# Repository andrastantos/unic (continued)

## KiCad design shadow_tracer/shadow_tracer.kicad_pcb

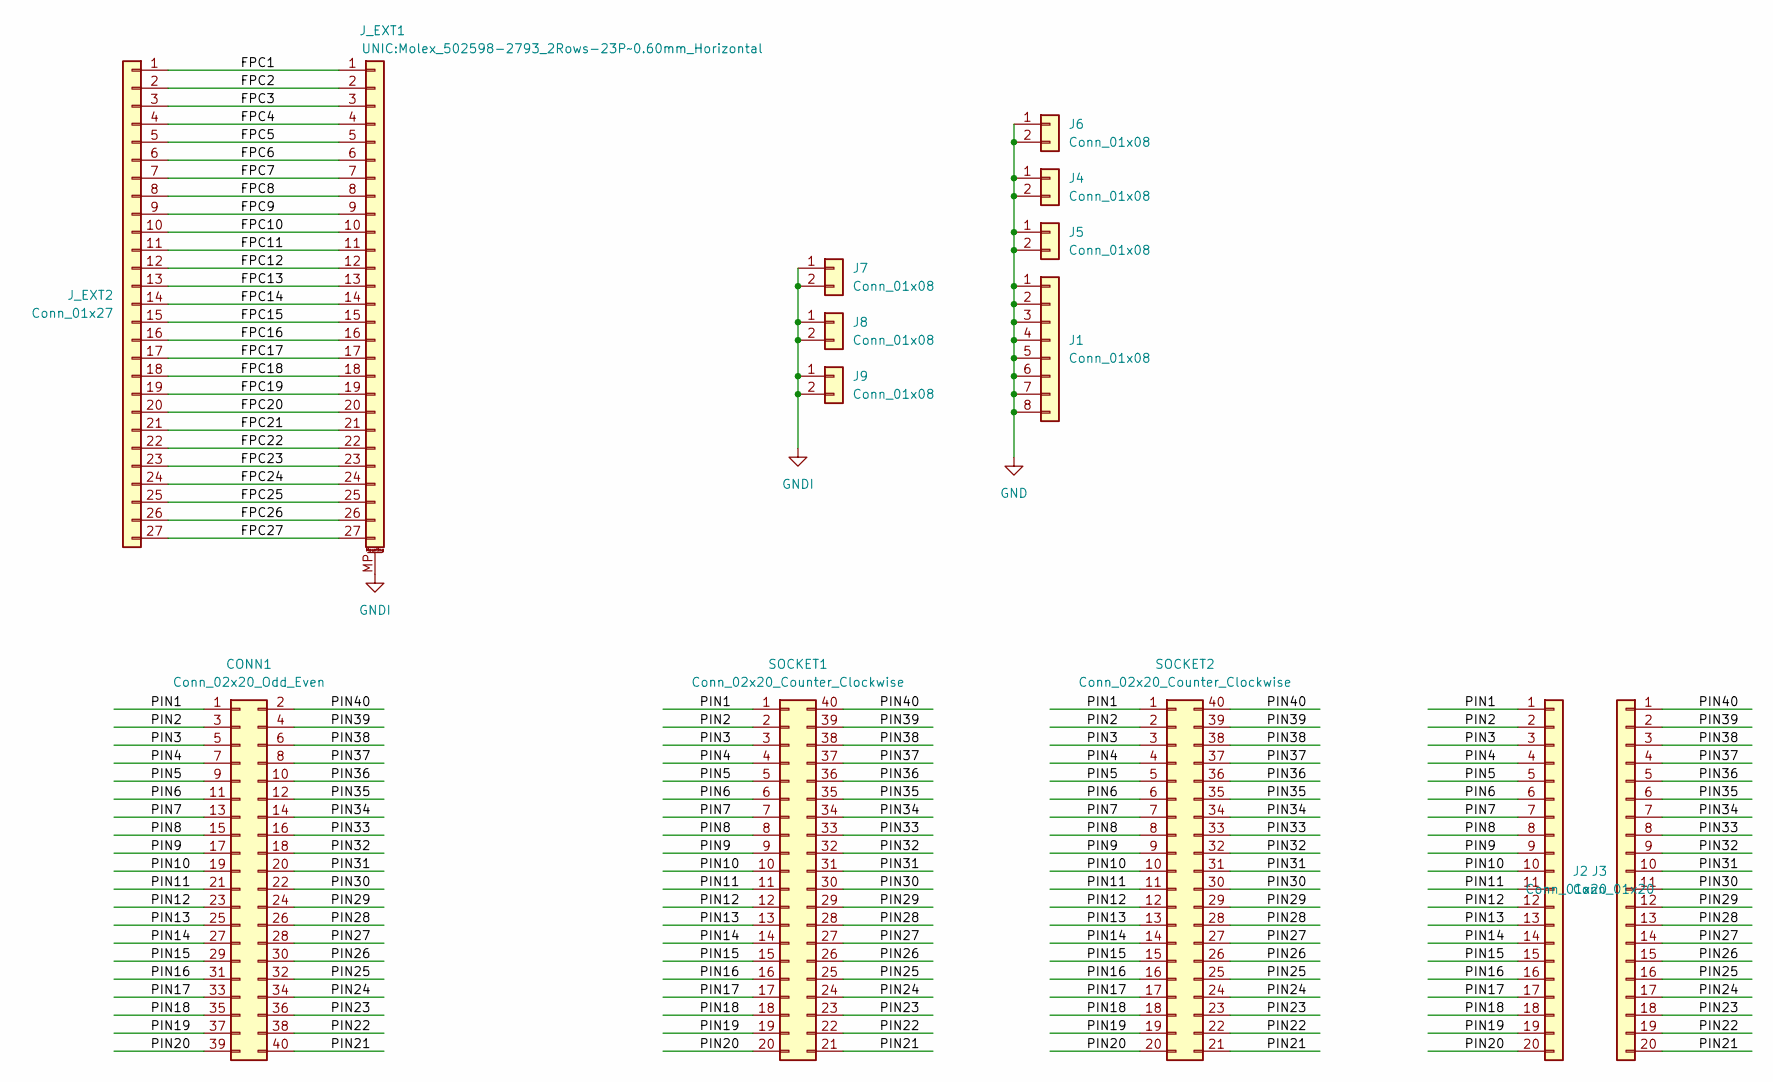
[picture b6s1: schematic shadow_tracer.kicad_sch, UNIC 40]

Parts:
CONN1: Conn_02x20_Odd_Even; PinSocket_2x20_P2.54mm_Horizontal
J1: Conn_01x08; PinHeader_1x08_P2.54mm_Vertical
J2, J3: Conn_01x20; PinHeader_1x20_P2.54mm_Vertical
J4, J5, J6, J7, J8, J9: Conn_01x08; PinHeader_1x02_P2.54mm_Vertical
J_EXT1: Conn_01x27_MountingPin; Molex_502598-2793_2Rows-23P~0.60mm_Horizontal
J_EXT2: Conn_01x27; PinHeader_2x14_P2.54mm_Vertical
SOCKET1, SOCKET2: Conn_02x20_Counter_Clockwise; DIP-40_W15.24mm_Socket_LongPads

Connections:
/FPC1: J_EXT1.1, J_EXT2.1
/FPC2: J_EXT1.2, J_EXT2.2
/FPC3: J_EXT1.3, J_EXT2.3
/FPC4: J_EXT1.4, J_EXT2.4
/FPC5: J_EXT1.5, J_EXT2.5
/FPC6: J_EXT1.6, J_EXT2.6
/FPC7: J_EXT1.7, J_EXT2.7
/FPC8: J_EXT1.8, J_EXT2.8
/FPC9: J_EXT1.9, J_EXT2.9
/FPC10: J_EXT1.10, J_EXT2.10
/FPC11: J_EXT1.11, J_EXT2.11
/FPC12: J_EXT1.12, J_EXT2.12
/FPC13: J_EXT1.13, J_EXT2.13
/FPC14: J_EXT1.14, J_EXT2.14
/FPC15: J_EXT1.15, J_EXT2.15
/FPC16: J_EXT1.16, J_EXT2.16
/FPC17: J_EXT1.17, J_EXT2.17
/FPC18: J_EXT1.18, J_EXT2.18
/FPC19: J_EXT1.19, J_EXT2.19
/FPC20: J_EXT1.20, J_EXT2.20
/FPC21: J_EXT1.21, J_EXT2.21
/FPC22: J_EXT1.22, J_EXT2.22
/FPC23: J_EXT1.23, J_EXT2.23
/FPC24: J_EXT1.24, J_EXT2.24
/FPC25: J_EXT1.25, J_EXT2.25
/FPC26: J_EXT1.26, J_EXT2.26
/FPC27: J_EXT1.27, J_EXT2.27
/PIN1: CONN1.1, J2.1, SOCKET1.1, SOCKET2.1
/PIN2: CONN1.3, J2.2, SOCKET1.2, SOCKET2.2
/PIN3: CONN1.5, J2.3, SOCKET1.3, SOCKET2.3
/PIN4: CONN1.7, J2.4, SOCKET1.4, SOCKET2.4
/PIN5: CONN1.9, J2.5, SOCKET1.5, SOCKET2.5
/PIN6: CONN1.11, J2.6, SOCKET1.6, SOCKET2.6
/PIN7: CONN1.13, J2.7, SOCKET1.7, SOCKET2.7
/PIN8: CONN1.15, J2.8, SOCKET1.8, SOCKET2.8
/PIN9: CONN1.17, J2.9, SOCKET1.9, SOCKET2.9
/PIN10: CONN1.19, J2.10, SOCKET1.10, SOCKET2.10
/PIN11: CONN1.21, J2.11, SOCKET1.11, SOCKET2.11
/PIN12: CONN1.23, J2.12, SOCKET1.12, SOCKET2.12
/PIN13: CONN1.25, J2.13, SOCKET1.13, SOCKET2.13
/PIN14: CONN1.27, J2.14, SOCKET1.14, SOCKET2.14
/PIN15: CONN1.29, J2.15, SOCKET1.15, SOCKET2.15
/PIN16: CONN1.31, J2.16, SOCKET1.16, SOCKET2.16
/PIN17: CONN1.33, J2.17, SOCKET1.17, SOCKET2.17
/PIN18: CONN1.35, J2.18, SOCKET1.18, SOCKET2.18
/PIN19: CONN1.37, J2.19, SOCKET1.19, SOCKET2.19
/PIN20: CONN1.39, J2.20, SOCKET1.20, SOCKET2.20
/PIN21: CONN1.40, J3.20, SOCKET1.21, SOCKET2.21
/PIN22: CONN1.38, J3.19, SOCKET1.22, SOCKET2.22
/PIN23: CONN1.36, J3.18, SOCKET1.23, SOCKET2.23
/PIN24: CONN1.34, J3.17, SOCKET1.24, SOCKET2.24
/PIN25: CONN1.32, J3.16, SOCKET1.25, SOCKET2.25
/PIN26: CONN1.30, J3.15, SOCKET1.26, SOCKET2.26
/PIN27: CONN1.28, J3.14, SOCKET1.27, SOCKET2.27
/PIN28: CONN1.26, J3.13, SOCKET1.28, SOCKET2.28
/PIN29: CONN1.24, J3.12, SOCKET1.29, SOCKET2.29
/PIN30: CONN1.22, J3.11, SOCKET1.30, SOCKET2.30
/PIN31: CONN1.20, J3.10, SOCKET1.31, SOCKET2.31
/PIN32: CONN1.18, J3.9, SOCKET1.32, SOCKET2.32
/PIN33: CONN1.16, J3.8, SOCKET1.33, SOCKET2.33
/PIN34: CONN1.14, J3.7, SOCKET1.34, SOCKET2.34
/PIN35: CONN1.12, J3.6, SOCKET1.35, SOCKET2.35
/PIN36: CONN1.10, J3.5, SOCKET1.36, SOCKET2.36
/PIN37: CONN1.8, J3.4, SOCKET1.37, SOCKET2.37
/PIN38: CONN1.6, J3.3, SOCKET1.38, SOCKET2.38
/PIN39: CONN1.4, J3.2, SOCKET1.39, SOCKET2.39
/PIN40: CONN1.2, J3.1, SOCKET1.40, SOCKET2.40
GND: J1.1, J1.2, J1.3, J1.4, J1.5, J1.6, J1.7, J1.8, J4.1, J4.2, J5.1, J5.2, J6.1, J6.2
GNDI: J7.1, J7.2, J8.1, J8.2, J9.1, J9.2, J_EXT1.MP (MountPin)

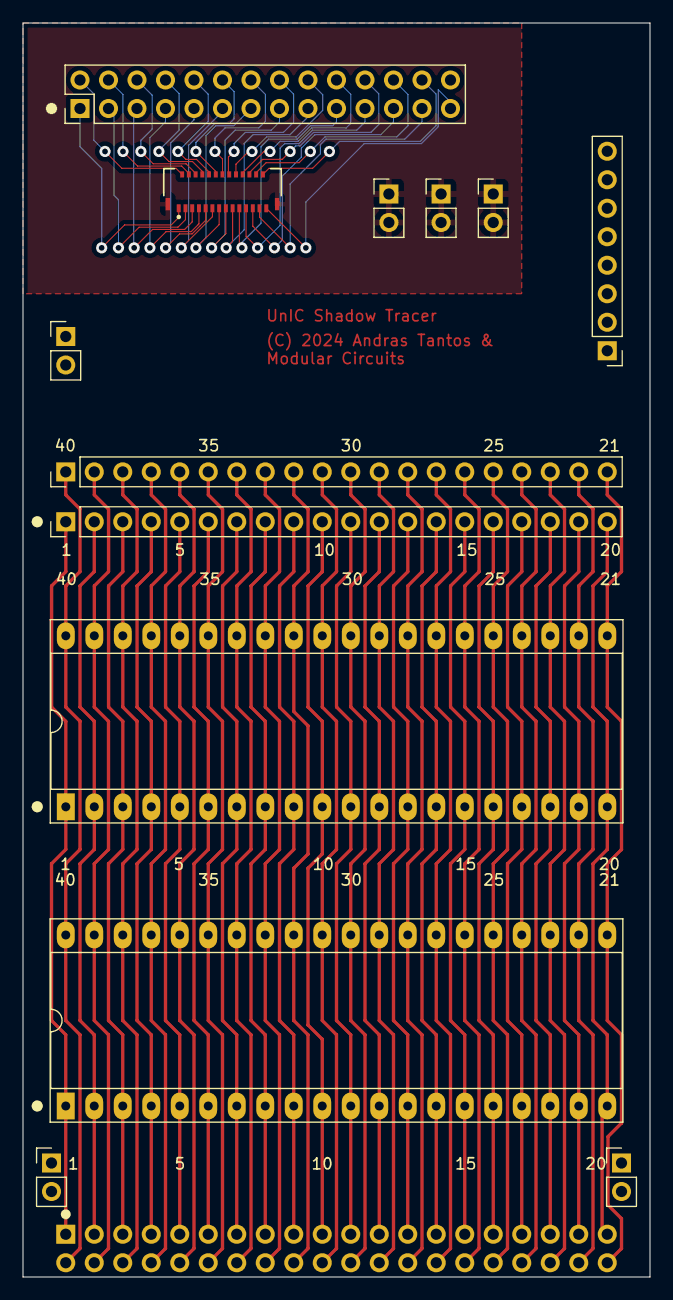
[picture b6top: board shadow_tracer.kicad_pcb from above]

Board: 2 copper layers, 55.9 x 111.8 mm, 14 parts (0 on the bottom side), 69 nets.

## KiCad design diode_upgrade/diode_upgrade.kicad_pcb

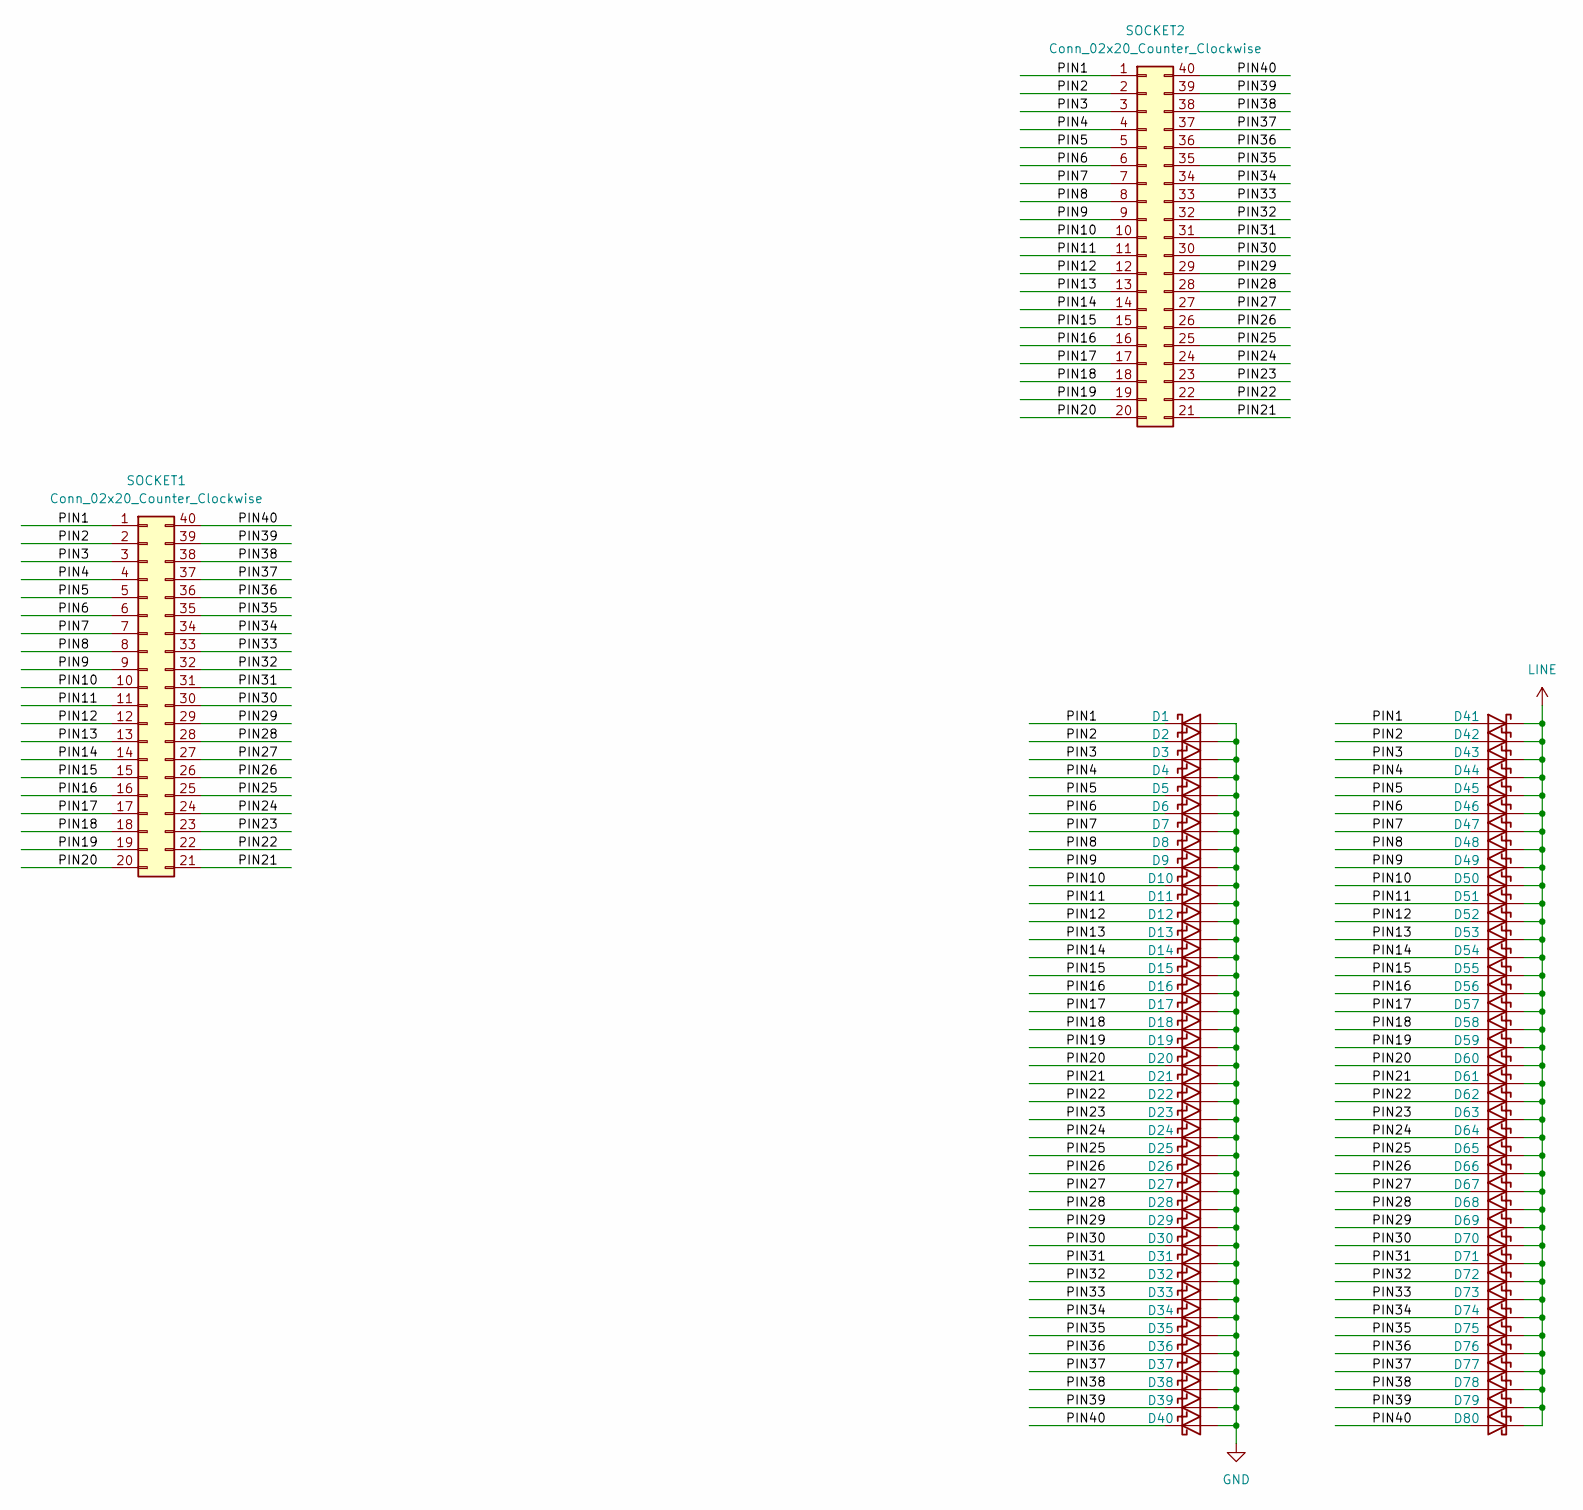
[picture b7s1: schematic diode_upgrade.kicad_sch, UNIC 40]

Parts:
D1, D2, D3, D4, D5, D6, D7, D8, D9, D10, D11, D12, D13, D14, D15, D16, D17, D18, D19, D20, D21, D22, D23, D24, D25, D26, D27, D28, D29, D30, D31, D32, D33, D34, D35, D36, D37, D38, D39, D40, D41, D42, D43, D44, D45, D46, D47, D48, D49, D50, D51, D52, D53, D54, D55, D56, D57, D58, D59, D60, D61, D62, D63, D64, D65, D66, D67, D68, D69, D70, D71, D72, D73, D74, D75, D76, D77, D78, D79, D80: D_Schottky; D_SOD-123; mpn SM5817PL-TP
SOCKET1: Conn_02x20_Counter_Clockwise; DIP-40_pin_header; mpn BA3760-TUBL-4A-F5
SOCKET2: Conn_02x20_Counter_Clockwise; DIP-40_W15.24mm_Socket_LongPads

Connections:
/PIN1: D1.1 (K), D41.2 (A), SOCKET1.1, SOCKET2.1
/PIN2: D2.1 (K), D42.2 (A), SOCKET1.2, SOCKET2.2
/PIN3: D3.1 (K), D43.2 (A), SOCKET1.3, SOCKET2.3
/PIN4: D4.1 (K), D44.2 (A), SOCKET1.4, SOCKET2.4
/PIN5: D5.1 (K), D45.2 (A), SOCKET1.5, SOCKET2.5
/PIN6: D6.1 (K), D46.2 (A), SOCKET1.6, SOCKET2.6
/PIN7: D7.1 (K), D47.2 (A), SOCKET1.7, SOCKET2.7
/PIN8: D8.1 (K), D48.2 (A), SOCKET1.8, SOCKET2.8
/PIN9: D9.1 (K), D49.2 (A), SOCKET1.9, SOCKET2.9
/PIN10: D10.1 (K), D50.2 (A), SOCKET1.10, SOCKET2.10
/PIN11: D11.1 (K), D51.2 (A), SOCKET1.11, SOCKET2.11
/PIN12: D12.1 (K), D52.2 (A), SOCKET1.12, SOCKET2.12
/PIN13: D13.1 (K), D53.2 (A), SOCKET1.13, SOCKET2.13
/PIN14: D14.1 (K), D54.2 (A), SOCKET1.14, SOCKET2.14
/PIN15: D15.1 (K), D55.2 (A), SOCKET1.15, SOCKET2.15
/PIN16: D16.1 (K), D56.2 (A), SOCKET1.16, SOCKET2.16
/PIN17: D17.1 (K), D57.2 (A), SOCKET1.17, SOCKET2.17
/PIN18: D18.1 (K), D58.2 (A), SOCKET1.18, SOCKET2.18
/PIN19: D19.1 (K), D59.2 (A), SOCKET1.19, SOCKET2.19
/PIN20: D20.1 (K), D60.2 (A), SOCKET1.20, SOCKET2.20
/PIN21: D21.1 (K), D61.2 (A), SOCKET1.21, SOCKET2.21
/PIN22: D22.1 (K), D62.2 (A), SOCKET1.22, SOCKET2.22
/PIN23: D23.1 (K), D63.2 (A), SOCKET1.23, SOCKET2.23
/PIN24: D24.1 (K), D64.2 (A), SOCKET1.24, SOCKET2.24
/PIN25: D25.1 (K), D65.2 (A), SOCKET1.25, SOCKET2.25
/PIN26: D26.1 (K), D66.2 (A), SOCKET1.26, SOCKET2.26
/PIN27: D27.1 (K), D67.2 (A), SOCKET1.27, SOCKET2.27
/PIN28: D28.1 (K), D68.2 (A), SOCKET1.28, SOCKET2.28
/PIN29: D29.1 (K), D69.2 (A), SOCKET1.29, SOCKET2.29
/PIN30: D30.1 (K), D70.2 (A), SOCKET1.30, SOCKET2.30
/PIN31: D31.1 (K), D71.2 (A), SOCKET1.31, SOCKET2.31
/PIN32: D32.1 (K), D72.2 (A), SOCKET1.32, SOCKET2.32
/PIN33: D33.1 (K), D73.2 (A), SOCKET1.33, SOCKET2.33
/PIN34: D34.1 (K), D74.2 (A), SOCKET1.34, SOCKET2.34
/PIN35: D35.1 (K), D75.2 (A), SOCKET1.35, SOCKET2.35
/PIN36: D36.1 (K), D76.2 (A), SOCKET1.36, SOCKET2.36
/PIN37: D37.1 (K), D77.2 (A), SOCKET1.37, SOCKET2.37
/PIN38: D38.1 (K), D78.2 (A), SOCKET1.38, SOCKET2.38
/PIN39: D39.1 (K), D79.2 (A), SOCKET1.39, SOCKET2.39
/PIN40: D40.1 (K), D80.2 (A), SOCKET1.40, SOCKET2.40
GND: D1.2 (A), D2.2 (A), D3.2 (A), D4.2 (A), D5.2 (A), D6.2 (A), D7.2 (A), D8.2 (A), D9.2 (A), D10.2 (A), D11.2 (A), D12.2 (A), D13.2 (A), D14.2 (A), D15.2 (A), D16.2 (A), D17.2 (A), D18.2 (A), D19.2 (A), D20.2 (A), D21.2 (A), D22.2 (A), D23.2 (A), D24.2 (A), D25.2 (A), D26.2 (A), D27.2 (A), D28.2 (A), D29.2 (A), D30.2 (A), D31.2 (A), D32.2 (A), D33.2 (A), D34.2 (A), D35.2 (A), D36.2 (A), D37.2 (A), D38.2 (A), D39.2 (A), D40.2 (A)
LINE: D41.1 (K), D42.1 (K), D43.1 (K), D44.1 (K), D45.1 (K), D46.1 (K), D47.1 (K), D48.1 (K), D49.1 (K), D50.1 (K), D51.1 (K), D52.1 (K), D53.1 (K), D54.1 (K), D55.1 (K), D56.1 (K), D57.1 (K), D58.1 (K), D59.1 (K), D60.1 (K), D61.1 (K), D62.1 (K), D63.1 (K), D64.1 (K), D65.1 (K), D66.1 (K), D67.1 (K), D68.1 (K), D69.1 (K), D70.1 (K), D71.1 (K), D72.1 (K), D73.1 (K), D74.1 (K), D75.1 (K), D76.1 (K), D77.1 (K), D78.1 (K), D79.1 (K), D80.1 (K)

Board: 2 copper layers, 82 parts (40 on the bottom side), 42 nets, no tracks yet.

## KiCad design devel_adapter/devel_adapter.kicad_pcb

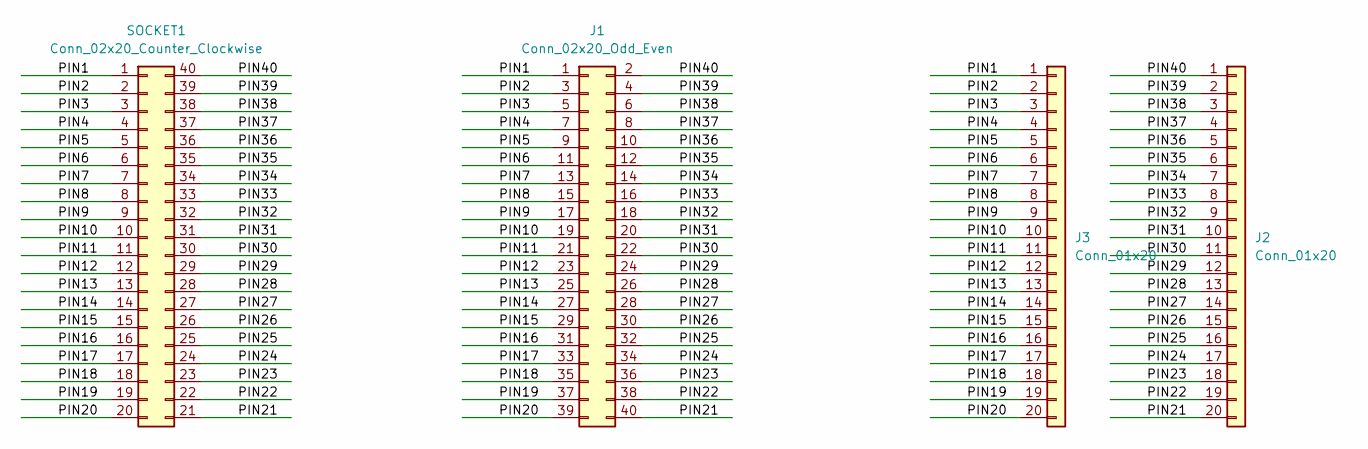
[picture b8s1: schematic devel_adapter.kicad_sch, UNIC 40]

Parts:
J1: Conn_02x20_Odd_Even; PinHeader_2x20_P2.54mm_Vertical
J2, J3: Conn_01x20; PinHeader_1x20_P2.54mm_Vertical
SOCKET1: Conn_02x20_Counter_Clockwise; DIP-40_pin_header

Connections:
/PIN1: J1.1, J3.1, SOCKET1.1
/PIN2: J1.3, J3.2, SOCKET1.2
/PIN3: J1.5, J3.3, SOCKET1.3
/PIN4: J1.7, J3.4, SOCKET1.4
/PIN5: J1.9, J3.5, SOCKET1.5
/PIN6: J1.11, J3.6, SOCKET1.6
/PIN7: J1.13, J3.7, SOCKET1.7
/PIN8: J1.15, J3.8, SOCKET1.8
/PIN9: J1.17, J3.9, SOCKET1.9
/PIN10: J1.19, J3.10, SOCKET1.10
/PIN11: J1.21, J3.11, SOCKET1.11
/PIN12: J1.23, J3.12, SOCKET1.12
/PIN13: J1.25, J3.13, SOCKET1.13
/PIN14: J1.27, J3.14, SOCKET1.14
/PIN15: J1.29, J3.15, SOCKET1.15
/PIN16: J1.31, J3.16, SOCKET1.16
/PIN17: J1.33, J3.17, SOCKET1.17
/PIN18: J1.35, J3.18, SOCKET1.18
/PIN19: J1.37, J3.19, SOCKET1.19
/PIN20: J1.39, J3.20, SOCKET1.20
/PIN21: J1.40, J2.20, SOCKET1.21
/PIN22: J1.38, J2.19, SOCKET1.22
/PIN23: J1.36, J2.18, SOCKET1.23
/PIN24: J1.34, J2.17, SOCKET1.24
/PIN25: J1.32, J2.16, SOCKET1.25
/PIN26: J1.30, J2.15, SOCKET1.26
/PIN27: J1.28, J2.14, SOCKET1.27
/PIN28: J1.26, J2.13, SOCKET1.28
/PIN29: J1.24, J2.12, SOCKET1.29
/PIN30: J1.22, J2.11, SOCKET1.30
/PIN31: J1.20, J2.10, SOCKET1.31
/PIN32: J1.18, J2.9, SOCKET1.32
/PIN33: J1.16, J2.8, SOCKET1.33
/PIN34: J1.14, J2.7, SOCKET1.34
/PIN35: J1.12, J2.6, SOCKET1.35
/PIN36: J1.10, J2.5, SOCKET1.36
/PIN37: J1.8, J2.4, SOCKET1.37
/PIN38: J1.6, J2.3, SOCKET1.38
/PIN39: J1.4, J2.2, SOCKET1.39
/PIN40: J1.2, J2.1, SOCKET1.40

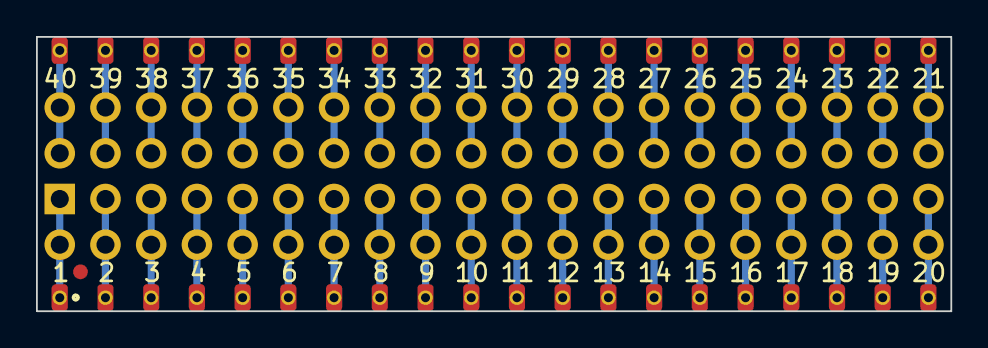
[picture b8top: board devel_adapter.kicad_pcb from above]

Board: 2 copper layers, 50.8 x 15.2 mm, 4 parts (0 on the bottom side), 40 nets.

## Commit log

2023-05-09 Unic project started.
2023-05-09 Whops, gitignore got to the wrong place.
2023-05-09 Gitignore updates.
2023-05-11 Added JTAG notes
2023-05-11 PCB file for unic
2023-05-11 Various datasheets added.
2023-05-12 More datasheets
2023-05-15 Added summary package datasheet.
2023-06-07 Added JFET-based protection sim. It seems to be working?
2023-06-16 Documentation update.
2023-06-26 More info on protection circuits.
2023-06-28 Large documentation update
2023-12-11 Much missing stuff added back
2023-12-11 Migrated cores
2023-12-11 Re-added submodules
2023-12-11 Added ESD diode from within FPGA.
    There is a transient on this diode when
    driven high hard from an external source.
    The length of the transient is about 7ns.
2023-12-13 Changed Espresso, added 8088 project.
2023-12-13 Added extra diodes to shunt ESD path.
2023-12-13 More simulation of high-voltage transients.
2023-12-19 GW1-based board is fully routed. Cleanup still needed!
2023-12-19 Some more sim experiments
2023-12-20 Much more GoWin documentation.
2023-12-20 Small fixes to board file
2023-12-20 Migrated to KiCad 7.
2023-12-20 Fixed GoWin part footprint reference.
2023-12-21 Board more or less done.
2023-12-25 Development board more or less done.
2023-12-25 Library changes related to development board.
2023-12-26 DIP adapter board for development board.
2023-12-26 Adapter board is production ready
2023-12-26 Added tiny DAC to library
2023-12-26 Devel board is production ready
2023-12-27 Added power input connector
2023-12-27 Added power jack with 3D model
2023-12-28 Replaced TSSOP FLASH with SO-8 one due to availability concerns.
2023-12-29 Updated FLASH part to package that's actually available.
2023-12-29 Updated footprints for LCD connector and PSRAM
2023-12-29 Populated part numbers for most parts.
2023-12-30 Reworked switcher components and layout.
2023-12-30 Switched back to 0805 caps: they're cheaper. TODO: part number updates.
2024-01-04 Ready to roll with DEVEL board!
2024-02-12 New documentation
2024-02-12 Devel updates.
2024-02-12 BOM checked in
2024-02-12 First FPGA project.
    This is also an attempt at a universal CST file, but the toolset is too
    brain-dead to allow for that. I will have to auto-generate this from
    a template once the Python flow is worked out.
2024-02-12 Code for first OLED test. Not tested in real HW, but simulation is promising.
2024-02-12 Some updated to UNIC GW1 based on post-release learnings.
2024-02-13 OLED controller works.
2024-02-15 Added PNG parser to OLED driver; added logo as well.
2024-02-16 Some outstanding changes to T13 board
2024-03-26 Simulation circuit updates.
2024-04-30 Updated board file; started cover CAD.
    This checkin marks the hopefully complete V1.0 design for the form-factor
    board.
    It also contains the first (incomplete) iteration of the cover design.
    It has a bunch of interference with components on the PCB which
    needs to be cleaned. It's also unclear if snaps have to be 1.5mm thick.
    Seems excessive. Finally, I don't think the OLED display can even survive
2024-05-01 Added test-points, edge clearance, some cleanup.
2024-05-03 Added fiducials and some other flourishes.
2024-05-05 Lots of (local) footprint cleanup and readying for board release.
2024-05-05 DRC-clean DIP-40 header.
2024-05-05 Fixed some footprints, fab drawings.
2024-05-31 Fixed GoWin part number
2024-05-31 Release files.
2024-05-31 Documentation drawings
2024-06-05 Changed PCB to match that of manufacturing:
    1. Removed solder paste from U1 (as it will be hand-soldered).
    2. Changed vias to have pads on top/bottom.
2024-08-04 ECO for switcher part change
2024-08-09 New diodes are added
    PCB is also fixed up, but fab notes
    need cleaning. Also, I need to select
    an actual diode.
2024-08-09 Updated diode part and footprint.
2024-08-09 Fixed fab notes
2024-08-12 Added some new datasheets.
2024-08-12 Started RP2350-based UnIC.
2024-08-12 Some diode simulations.
2024-08-12 Small DIP exercises.
2024-08-12 More work towards RP based UnIC
    The IO connections are mostly figured out, component placement
    as well. Still need new inductor, proper XTAL, USB and of course
    a lot of routing, including power.
2024-08-13 More work towards UnIC-RP. This time power supplies are cleaned up a bit.
2024-08-13 Some notes about SWDBG over USB-C
2024-08-13 Much more complet RP schematic.
    The USB-based debug setup is now drawn up. Component
    placement is also complete. A thorough review is needed
    especially on component footprints!
2024-08-14 More notes, this time with actual repro in LA.
2024-08-14 Missed USB connector model.
2024-08-14 Lots of work towards PIP issues.
2024-08-14 More work towards routing RP board.
2024-08-15 More or less complete schematic.
    Component selection is not final, but functionality around
    USB-C connector is. We even have UART output on it now as
    well as USB VBUS detection and control on the right pins.
2024-08-15 Component selection I think now is complete.
2024-08-15 Board fully routed except for power.
2024-08-16 Work towards power routing
2024-08-16 More or less complete routing.
    There are a few clearance violations with NPTH that doesn't
    make sense. Also, power planes are not in yet, only wires.
2024-08-18 Shadow tracer board.
    This is a board that (with the proper core) can shadow a to-be-simulated
    IC with its UnIC equivalent and trigger on any waveform mismatches.
    It can be used to quickly track down differences in behavior between
    the real and the UnIC versions of implementations.
2024-08-18 More notes on experiments.
2024-08-19 Diode upgrade PCB.
    This little guy would go underneath a UnIC V1.0 board
    and upgrade all the diodes with proper Schottky ones.
    Then GND and LINE wold need to be blue-wired over to
    UnIC to make the whole contraption work.
2024-08-20 Programmer more or less complete.
    Missing LEDs, I guess.
2024-08-20 Release package for programmer.
2024-08-20 True release package for programmer.
2024-08-21 Added BOM notes
2024-08-21 Shadow tracer release package.
2024-09-03 Much UnIC RP cleanup.
2024-09-04 Second programmer variant.
2024-09-04 Finished programmer 2.
2024-09-04 Beautified schematic and PCB for programmer 2.
2024-09-08 Some note updates
2024-09-08 Programmer bring-up changes and notes
2024-09-08 Updated programmer schematic and PCBs.
    All known changes are incorporated.
    p.s.: I decided to stick with this rather sketchy LDO.
    The reason for this is that it's heatsink tab is connected
    to VCC, which happens to be the fill on the top layer
    so a GND-connected alternative would be less well cooled.
2024-09-12 Many many more comments.
2024-09-13 Some quick schematic beautification.
2024-09-27 I think I have found and fixed the PIP boot issue.
    Indeed it was a T80 issue, a race-condition between setting IFF1 from
    EI or RETN and clearing it due to a concurrent NMI.
2024-09-27 Started Z80 sampler project.
2024-09-29 Z80 sampler project complete.
2024-09-29 Changed visible layers.
2024-10-23 Release package
2024-10-23 Ziped release package.
2024-12-28 Some leads on PLCC interfaces.
    Expensive as hell, but at least existing.
2024-12-31 Picking up OLED controller work.
2024-12-31 Some cleanup.
2024-12-31 Removed blinking of OLED display.
2025-01-09 cover has now some room for pins
2025-01-10 Started integrated USB programmer variant of UnIC.
    This is far from done, but shows some hope for fitting.
2025-01-10 Added new OLED display "datasheet".
    This should be more or less functionally compatible to the
    old one, but much more widely available and cheaper (on AliBaba), being the form factor that's used in the Ledger
    nano S thingy.
    It is configured as 4-wire SPI (i.e. separate C/D pin), which is a
    bit of a bummer, but what can you do.
2025-01-10 Some small outstanding changes.
2025-01-10 Whops, failed to save schematic before commit.
2025-01-10 Integrated JTAG controller mostly routed.
    There are still some keepout violations and power nets
    are incomplete, but at least there's a light at the end
    if the tunnel.
2025-01-13 UnIC with FT232H is fully routed.
    Not all that nicely, power needs a lot more work. But at least
    connectivity is there.
2025-01-13 UnIC wuth ISB (V2.0) is pretty much complete.
2025-01-14 Brought UnIC V1 up to date with latest changes.
    Updated OLED display connector and pinout
    Added DC/DC 33pF cap
    Added keepouts on bottom side for case clamps
2025-01-14 Small keepout shape cleanup on UnIC V2
2025-01-17 Some cleanup
2025-01-17 Some progress towards 32-pin UnIC variant.
    Components are more or less placed, routing is not done.
2025-01-22 24-pin UnIC is fully routed.
2025-01-22 Cleaned up some shapes, added series resistor to clock.
2025-01-24 Planes are flooded for 24-pin design.
2025-01-24 Restarted 40-pin design with learnings from the 24-pin one.
2025-01-24 Some progress with 40-pin board.
    In the end, it might not be any better than the old one.
    We shall see...
2025-01-27 Some progress on 40-pin USB
